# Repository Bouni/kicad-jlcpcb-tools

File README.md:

#  KiCAD JLCPCB tools

***

***

***

Plugin to generate all files necessary for JLCPCB board fabrication and assembly

- Gerber files
- Excellon files
- BOM file
- CPL file
- JLCPCB controlled-impedance workbook and self-contained HTML companion, when enabled for the board

Furthermore it lets you search the JLCPCB parts database and assign parts directly to the footprints which result in them being put into the BOM file.

On KiCad 10 boards with named [design variants](#design-variants-kicad-10),
compare and edit variants side by side and generate separate fabrication outputs.

## Installation 💾

### KiCAD PCM

Add my custom repo to *the Plugin and Content Manager*, the URL is:

```sh
https://raw.githubusercontent.com/Bouni/bouni-kicad-repository/main/repository.json
```

From there you can install the plugin via the GUI.

### Git

Clone this repo into your KiCad `scripting/plugins` folder.

> [!TIP]
> You can open the plugins directory directly from KiCad to avoid locating the path manually:
> In the *PCB Editor*, choose **Tools → External Plugins → Open Plugin Directory** (or **Reveal Plugin Folder in Finder** on macOS), or open **Preferences → PCB Editor → Action Plugins** and click the folder icon. From that directory, open a terminal and run `git clone https://github.com/Bouni/kicad-jlcpcb-tools.git`.

Alternatively, navigate to the folder in your terminal:

**Windows (Command Prompt)**

```cmd
cd "%USERPROFILE%\Documents\KiCad\<version>\scripting\plugins"
git clone https://github.com/Bouni/kicad-jlcpcb-tools.git
```

**Windows (PowerShell)**

```powershell
cd "$HOME\Documents\KiCad\<version>\scripting\plugins"
git clone https://github.com/Bouni/kicad-jlcpcb-tools.git
```

**Linux**

```sh
cd ~/.local/share/kicad/<version>/scripting/plugins
git clone https://github.com/Bouni/kicad-jlcpcb-tools.git
```

**macOS**

```sh
cd ~/Documents/KiCad/<version>/scripting/plugins
git clone https://github.com/Bouni/kicad-jlcpcb-tools.git
```

> [!NOTE]
> `<version>` can be `7.0`, `8.0`, `9.0`, or `X.YY` depending on the version you use. You may need to create the `scripting/plugins` folder if it does not exist.

After cloning, choose **Tools → External Plugins → Refresh Plugins** in the *PCB Editor* (or restart KiCad) to load the plugin.

### Flatpak :warning:

The Flatpak installation of KiCAD currently does not ship with pip and requests installed. The later is required for the plugin to work.
In order to get it working you can run the following 3 commands:

1. `flatpak run --command=sh org.kicad.KiCad`
2. `python -m ensurepip --upgrade`
3. `/var/data/python/bin/pip3 install requests`

See [issue #94](https://github.com/Bouni/kicad-jlcpcb-tools/issues/94) for more info.

## Usage 🥳

To access the plugin choose `Tools → External Plugins → JLCPCB Tools` from the *PCB Editor* menus

Checkout this screencast, it shows quickly how to use this plugin:

### Design variants (KiCad 10+)

Create named variants in KiCad and transfer them to the PCB to use the variant
table. Boards without named variants keep the ordinary parts table.

- **Compare variants side by side**, with Ref, Footprint, Side, PCB angle, and Correction columns fixed on the left when space permits. Ref stays fixed in narrower windows.
- **Spot differences quickly** through highlighted settings and yellow outlines around the affected variant’s cells in each component row.
- **Focus on differing component settings** with **Differences only** in the toolbar above the table.
- **Edit each variant independently:** Value, LCSC assignment, and BOM/POS/POP (populated) flags. Select components within one variant for batch assignments, flag changes, and copying.
- **Copy and paste selected components between variants:** Copy transfers Value, LCSC and BOM/POS/POP settings for every selected component; select the same components in another variant and Paste. Use **Copy cell value** for an individual value, or **Copy to variants…** to choose fields and destination variants.
- **Drag variant headers to reorder them** and bring variants together for comparison.
- **Compare price and stock availability** using compact indicators and hover details.
- **Choose an Output variant** to generate its BOM, placement, and fabrication files.
- **Review placement corrections for the Output variant** in the Correction column. Exact LCSC rules follow that variant's assigned part; pattern rules use Default's reference, Value, and placed footprint.

Assignments and flags are stored in the KiCad board; save the PCB to preserve edits.

The examples below use sample component data in the main JLCPCB Tools
window. Pointer and click cues make the actions easier to follow.

#### Edit settings and see differences

Change a setting in one variant to compare it with **Default**. Here,
turning off **POP** (populated) for **R4** in **Economy** highlights the
changed cell and outlines Economy’s cells in that row. The yellow outline
remains visible while the row is selected.

Turn POP back on to match Default and clear R4’s difference highlight.

#### Show differences only

Select **Differences only** in the toolbar above the table to focus on
differing component settings. In this example, enabling the checkbox
leaves **R1** and **R3** visible. Clear it to bring all five rows back.

#### Reorder variant columns

Drag a variant header to move its entire group of columns. Here,
**Premium** moves before **Economy**.

The translucent column preview follows the pointer, while the insertion
marker and **Drop before Economy** label show the destination. Release the
header to change the order to **Default**, **Premium**, **Economy**.

### Controlled impedance

Controlled impedance is an option that JLCPCB offers. To convey which traces should be impedance matched JLCPCB requires a `Required_impedance_control.xlsx` to be included in the design .zip file. If one is not included in your design package, JLCPCB will contact you and request that you provide this file.

It can be somewhat time consuming and repetative to update this file each time your layout changes, but not any more. This plugin can automatically generate the complete `Required_impedance_control.xlsx` file, including target impedances, reference layers AND all of the highlighted nets from the layout.

Generation also includes a self-contained `Required_impedance_control.html` companion in the board's Gerber ZIP for web viewing of the generated output.

Review tracking records the latest workbook-preview view time and each signal layer's approval time in that same database. Image-view dates are hidden during review; the HTML companion shows UTC and distinguishes current from historical captures/settings. Older records show **Not recorded**. Timestamps are saved with the configuration, not on Cancel, and do not replace the required image/layer review.

For inspection and regression testing, [two combined RF example boards](examples/impedance/README.md) cover short and long top/bottom/inner routes, single-ended and differential coplanar/noncoplanar designs, and layer transitions with different widths. These repository test assets are separate from production settings; their impedance dimensions are nominal, not solver-certified.

## Keyboard shortcuts

Windows can be closed with ctrl-w/ctrl-q/command-w/command-w (OS dependent) and escape.
Pressing enter in the keyword text box will start a search.

### Toggle BOM / CPL attributes

You can easily toggle the `exclude from BOM` and `exclude from CPL` attributes of one or multiple footprints.

### Select LCSC parts from the JLCPCB parts database

Select one or multiple footprints, click select part. You can select parts with equal value and footprint using the Select alike button.
In the upcoming modal dialog, search for parts, select the one of your choice and click select part.
The LCSC number of your selection will then be assigned to the footprints.

To type or paste an LCSC number instead, right-click the selected footprints and choose **Enter LCSC…**. It accepts a part number such as `C25804` or a product link copied from lcsc.com or jlcpcb.com. The number may be one the downloaded parts library does not list: JLC can still assemble LCSC-only parts it buys in through pre-order or global sourcing, and your library may be older than the part. The plugin asks once before assigning such a number. With no library downloaded there is nothing to check against, so it assigns without asking.

The part selector helps the same way: search for one LCSC number, and if the results don't show that exact part, a button beside the result count assigns it with one click.

### Automatic schematic saving

Closing JLCPCB Tools saves its LCSC assignments and supported BOM settings to
the project's schematics. The manual **Export to schematic** button has been
removed. On boards with design variants, this always saves **Default**;
selecting a named variant for fabrication does not change the schematic source.

A missing assignment field preserves the schematic's existing part number;
an explicit empty assignment clears it. Invalid or conflicting assignments are
preserved and reported while safe assignments still save. Footprints are linked
to symbols by KiCad's UUID paths, so changed or duplicate references do not
redirect a save. PCB-only footprints need no schematic update. Stale or ambiguous
links are preserved and reported.
For reused sheets, a shared field is updated only when every instance is linked
and agrees on that field. A linked multi-unit component updates all authenticated
units together; incomplete or ambiguous component membership is preserved.

Ordinary unassigned parts and PCB-only footprints close quietly. If an unassigned
PCB footprint has a part number in the schematic, use KiCad's **Update PCB from
Schematic** to transfer it to the board. This is an advisory, not a save failure.
When a conflict, invalid assignment, or unresolved link needs attention, the plugin keeps the complete report
at `jlcpcb/schematic-save-report.txt`, identifying affected footprints and the
reasons. Interactive closing also shows a warning; forced shutdown saves the
report without a prompt. A later complete save removes an outdated report.
Safe partial saves can complete; they do not authorize archival of active legacy
recovery data.

Projects that already have a `jlcpcb/project.db` see a one-time notice explaining
that the schematic is now the durable store. Before the first automatic write,
the plugin also keeps a permanent zip at
`jlcpcb/schematics-before-plugin-attributes.zip` so you can restore the previous
sheets if needed.

The plugin uses the project's associated schematics and preserves an `_old`
backup for each file it writes. Projects without an associated schematic close
without writing one. If a schematic is locked, the default **Cancel** keeps the
plugin open so you can close Schematic Editor and retry. **Save Anyway** approves
only the listed locks; **Close without saving** leaves the schematic unchanged.
Save errors also let you keep the window open or close without saving the
remaining changes. Earlier sheets may already have been saved if a later write
fails. A forced application shutdown cannot wait for these prompts: locked or
failed saves are logged and the window closes.

This saves schematic files. Use KiCad's PCB save command to persist changes to
the PCB itself. An already-open Schematic Editor does not reload exported files
automatically and can overwrite them if you choose **Save Anyway**.

### Where part assignments are stored

The live KiCad board is the sole source of LCSC assignments, with or without
named design variants. Selecting, pasting, or clearing a part updates the native
footprint fields or the selected variant's fields. **Save the PCB in KiCad to
persist these changes.** Refreshing the plugin reads the current board, including
edits made outside the plugin.

Both table modes recognize `LCSC`, `JLC`, and `JLCPCB` assignment fields,
optionally followed by `Part`, `Part Number`, `Part Num`, `Part No`, `PartNr`,
`PN`, `Number`, `Code`, or `ID`; case, spaces, and punctuation are ignored.
Conflicting or invalid assignments appear unassigned. Selecting or clearing a part updates
all recognized assignment fields together. Assignments and schematic saves preserve
existing alias names. A nonempty assignment creates a hidden `LCSC` field when no
recognized alias exists. Other prefixed fields, such as `JLCPCB Rotation` or
`LCSC custom code`, remain metadata; move part numbers from such fields into a
recognized assignment field.

*KiCad Symbol Properties with sample data for a 10k 0603 resistor (C25804).*

Previously, ordinary boards used database or CSV assignments while boards with
named variants read native fields. Editing or clearing Default, then removing
the last named variant, could therefore restore an obsolete database assignment.
Both modes now read and edit the board; the former schematic/database priority
setting no longer applies.

On opening, the plugin checks an existing `jlcpcb/project.db` for recoverable
legacy assignments before applying part preferences or displaying the initial
BOM. It imports a valid LCSC number only when the board assignment field is
missing and the reference, value, footprint, and BOM/POS flags exactly match
the historical row. Every linked schematic unit must also have no assignment or
the same part number. PCB-only footprints and projects confirmed to have no
schematic can recover directly into native fields, even if the PCB retains old
symbol paths. Unreadable project files and missing declared sheets do not count
as an absent schematic. KiCad 10's generated placeholder for a layout-only
project does not require a schematic file. Within a discovered hierarchy, stale
or ambiguous links remain unresolved.
Existing native values, explicit clears, invalid or conflicting
fields, unresolved links, and disagreeing shared instances are preserved.
Recovery imports neither stock nor flags and does not require a parts catalog.
Save the PCB to retain recovered assignments.

Once recovery is durable in the saved schematic or PCB, the active `part_info`
table is renamed to `part_info_retired`, preserving its rows and schema. Existing
archives remain intact; later archives use names such as `part_info_retired_2`.
The plugin rechecks the table's schema and data inside the archive transaction
so another window's changes cannot be archived using an outdated recovery check.
Before archival, the plugin reads the saved current PCB and sibling PCBs in the
same directory. macOS AppleDouble metadata sidecars are excluded. Recovery needed
by another board stays active, including recovery needed by temporary PCB copies.
The migration report names blocking sibling files and repeats only new notices;
acknowledgment does not allow archival. Obsolete rows can
be archived only when those saved boards confirm they are no longer needed;
an unsaved deletion or footprint change is insufficient. Native-only recovery
stays active until you explicitly save the PCB. The plugin never saves it for
you. Cancellation, incomplete saves, unresolved recovery, and unreadable saved
boards retain the recovery table for a later retry.

The durable `jlcpcb/legacy-migration-report.json` records the source board, old
legacy value, chosen native value or clear, and the reason for each recovery
decision, retaining original provenance and the latest board snapshot without
adding a full snapshot for every session. It survives schematic-report cleanup
and archival. When an existing native value or explicit clear supersedes a
legacy number, an interactive close
shows the previously unseen decisions once. Forced shutdown leaves that notice
pending for the next interactive close. Failed audit writes retain recovery data
and retry later without reapplying imported assignments. If the audit still cannot
be written, keep the plugin open to retry. Explicitly closing without the audit
or forcing shutdown can lose observations that could not be written to disk.

Archived assignments are never imported again, and legacy CSV files are never
automatically imported. Archival preserves generation counters, corrections,
other tables, and CSV files. Reading or refreshing assignments does not create
or modify `part_info`; the notice acknowledgment and generation counter use
the separate `metadata` table.

Supplier descriptions and other part details are cached in memory by LCSC
number and fetched again as needed. A part's assembly process and
Standard-only class are the exception: they are saved by LCSC number in
`global.db` in the data folder, so a board opened again shows them at once,
and they are fetched again in the background once they are 30 days old.
Stock and pricing come from the currently selected parts catalog; they are
not persisted as board assignments.

### Part preferences

Part preferences remember which LCSC part to use for a value and footprint combination across projects. Two independent settings are enabled by default:

- **Remember my part preferences** remembers each successful part selection or pasted LCSC assignment. The latest explicit assignment replaces the preference; opening a board does not change preferences.
- **Parts preferences fill in empty LCSC assignments** fills blank LCSC assignments once each time the plugin window opens. Existing assignments are preserved. DNP parts and parts excluded from BOM or POS are skipped.

Applying part preferences, including automatic filling on opening, writes the
native board fields. Save the PCB to keep those assignments.

Clearing an LCSC assignment keeps its part preference, so an eligible blank assignment may fill again on the next opening. Exclude the part or disable automatic filling to keep it blank. The right-click actions **Save part preferences** and **Apply part preferences** remain available even when automation is disabled. Use **Part preferences** to delete, import, or export preferences. Deleting a preference does not remove assignments from your boards.

### Generate fabrication data

Generate all necessary assembly files for your board with a simple click.

A new directory called `jlcpcb` is created, and in there, two separate folders are created, `gerber` and `production_files`.

In `gerber/<board-name>`, all necessary `*.gbr` and `*.drl` files are generated and zipped into the `production_files` folder, ready for upload to JLCPCB. Each board has a separate plotting directory.
The zipfile is named `GERBER-<projectname>.zip`

Also in the `production_files` folder, two files are generated, `BOM-<projectname>.csv` and `CPL-<projectname>.csv`.

Footprints are included into the BOM and CPL files according to their `exclude from BOM` and `exclude from POS` attributes.

A footprint's CPL `Mid X`/`Mid Y` is the center of the bounding box of its soldered pads: NPTH holes and paste-only pads are left out, and a footprint without soldered pads uses its own position.

Optional pre/post generation hook scripts can be configured in settings.

- The pre-hook runs before generation and can block generation on failure (with Continue/Cancel prompt).
- The post-hook runs only after successful generation.

See [HOOKS.md](HOOKS.md) for configuration details and available environment variables.

### Export Additional JLC Specific Layers

Some boards you have manufactured will require additional layers in your Gerber. For example, when manufacturing flex PCBs with a stiffener, JLC requires a layer outlining the stiffener layer (top/bottom), dimensions and the stiffener material properties (material, thickness etc). Export these additional JLC specific layers in your production files with a simple modification.

Additional layers can be exported by creating layers with `JLC_` as the prefix of the layer name. You can access and edit the layer names in *Board Setup/Board Stackup/Board Editor Layers*

This tool will automatically export all additional layers with the JLC_ prefix and add them to the production files in `GERBER-<projectname>.zip`

## Footprint rotation correction

JLCPCB seems to need corrected rotation information. @matthewlai implemented that in his [JLCKicadTools](https://github.com/matthewlai/JLCKicadTools) and I adopted his work in this plugin as well.
You can download Matthews file from GitHub and manage your own corrections in the Rotation manager.

See [Importing and repairing corrections](CORRECTIONS.md) for supported CSV
formats, validation rules, and recovery of invalid records from older versions.

## Icons

This plugin makes use of a lot of icons from the excellent [Material Design Icons](https://materialdesignicons.com/)

## Development

1. Fork repo
2. Git clone forked repo
3. Install pre-commit `pip install pre-commit`
4. Setup pre-commit `pre-commit run`
5. Create feature branch `git switch -c my-awesome-feature`
6. Make your changes
7. Commit your changes `git commit -m "Awesome new feature"`
8. Push to GitHub `git push`
9. Create PR

Make sure you make use of pre-commit hooks in order to format everything nicely with `black`
In the near future I'll add `ruff` / `pylint` and possibly other pre-commit-hooks that enforce nice and clean code style.

### Tests

With Docker and [`act`](https://nektosact.com/installation/) installed, run the
complete test workflow:

```sh
python scripts/run_tests.py
```

See [testing instructions](docs/testing.md) for architecture and output options.

### Settings

`default_settings.json` holds the settings a fresh install starts from and is the only
settings file tracked in git. The plugin writes the settings you actually use to
`settings.json` beside it, which is git-ignored, so toggling a checkbox while developing
no longer shows up as a change to commit.

On every launch the stored settings are layered over the defaults, so a setting added by
a newer version arrives with its default rather than being missing. Add new settings to
`default_settings.json`; `tests/test_settings_defaults.py` fails if a setting the code
reads has no default shipped for it.

## How to rebuild the parts database

The parts database is rebuilt by the [update_parts_database.yml GitHub workflow](https://github.com/Bouni/kicad-jlcpcb-tools/blob/main/.github/workflows/update_parts_database.yml)

You can reference the steps in the 'Update database' section for the commands to run locally.

## python libraries

lib/ contains the necessary python packages that may not be a part of the KiCad python distribution.

These packages include:

- packaging

To install a package, such as 'packaging':

```python
pip install packaging --target ./lib
```

To update these packages:

```python
pip install packaging --upgrade --target ./lib
```

Future versions of KiCad may have support for a requires.txt to automate this process.

## Standalone mode

Allows the plugin UI to be started without KiCAD, enabling debugging with an IDE like pycharm / vscode.

Standalone mode is under development.

### Limitations

- All board / footprint / value data are hardcoded stubs, see standalone_impl.py

### How to use

To use the plugin in standlone mode you'll need to identify three pieces of information specific to your Kicad version, plugin path, and OS.

#### Python

The <i><b>{KiCad python}</b></i> should be used, this can be found at different locations depending on your system:

| OS     | Kicad python                                                                                |
|--------|---------------------------------------------------------------------------------------------|
|Mac     | /Applications/KiCad/KiCad.app/Contents/Frameworks/Python.framework/Versions/3.9/bin/python3 |
|Linux   | /usr/bin/python3                                                                            |
|Windows | C:\Program Files\KiCad\8.0\bin\python.exe                                                   |

#### Working directory

The <i><b>{working directory}</b></i> should be your plugins directory, ie:

| OS     | Working dir                                                |
|--------|------------------------------------------------------------|
|Mac     | ~/Documents/KiCad/<version>/scripting/plugins/             |
|Linux   | ~/.local/share/kicad/<version>/scripting/plugins/          |
|Windows | %USERPROFILE%\Documents\KiCad\<version>\scripting\plugins\ |

> [!NOTE]  
> <version> can be 7.0, 8.0, 9.0, or X.YY depending on the version you use

#### Plugin folder name

The <i><b>{kicad-jlcpcb-tools folder name}</b></i> should be the name of the kicad-jlcpcb-tools folder.

- For Kicad managed plugins this may be like

> com_github_bouni_kicad-jlcpcb-tools

- If you are developing kicad-jlcpcb-tools this is the folder you cloned the kicad-jlcpcb-tools as.

#### Command line

- Change to the working directory as noted above
- Run the python interpreter with the <i><b>{kicad-jlcpcb-tools folder name}</b></i> folder as a module.

For example:

```sh
cd {working directory}
{kicad_python} -m {kicad-jlcpcb-tools folder name}
```

For example on Mac:

```sh
/Applications/KiCad/KiCad.app/Contents/Frameworks/Python.framework/Versions/3.9/bin/python3 -m kicad-jlcpcb-tools
```

For example on Linux:

```sh
cd ~/.local/share/kicad/8.0/scripting/plugins/ && python -m kicad-jlcpcb-tools
```

For example on Windows:

```cmd
& 'C:\Program Files\KiCad\8.0\bin\python.exe' -m kicad-jlcpcb-tools
```

#### IDE

- Configure the command line to be '{kicad_python} -m {kicad-jlcpcb-tools folder name}'
- Set the working directory to {working directory}

If using PyCharm or Jetbrains IDEs, set the interpreter to Kicad's python, <i><b>{Kicad python}</b></i> and under 'run configuration' select Python.

Click on 'script path' and change instead to 'module name',
entering the name of the kicad-jlcpcb-tools folder, <i><b>{kicad-jlcpcb-tools folder name}</b></i>.

## How to release new versions of this plugin

[bouni-kicad-repository](https://raw.githubusercontent.com/Bouni/bouni-kicad-repository/main/repository.json) contains the
files for the latest version of the plugin, in the format KiCAD expects from external plugins.

To release a new version of this plugin:

1. In the <b>kicad-jlcpcb-plugin</b> repository:
   1. Visit the releases page 
   1. Click on 'Choose a tag', enter the next release number, say 2025.04.01 for example, and click on 'Create Tag' 
   1. Click 'Generate release notes' 
   1. If the release notes looks good, click on 'Publish release' 
1. Automatically the new release will trigger the 'kicad-pcm' workflow which will:
   1. Pull the latest plugin tag
   1. Create the appropriate pcm archive
   1. Upload the zip as an asset to a new GitHub release
   1. benc-uk/workflow-dispatch@v1 is used to trigger the 'Rebuild repository' workflow in [bouni-kicad-repository](https://github.com/Bouni/bouni-kicad-repository)
1. Automatically in the <b>bouni-kicad-repository</b>, the 'Rebuild repository' (rebuild.yml) workflow runs 'generate.py'
   1. generate.py updates .json and the latest .zip file using the release assets from the kicad-jlcpcb-plugin repository
1. The plugin should now be visible to users via the plugin manager.

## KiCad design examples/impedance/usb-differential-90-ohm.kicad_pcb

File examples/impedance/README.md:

# Two impedance review boards

| Open in KiCad | Target | Connectors | Circuits |
| --- | ---: | --- | ---: |
| [Single-ended RF / 50 ohm](single-ended-50-ohm.kicad_pcb) | 50 Ω | SMA, two per circuit | 14 |
| [USB differential / 90 ohm / 8 mil pair gap](usb-differential-90-ohm.kicad_pcb) | 90 Ω | USB-C, two per circuit | 14 |

Each project is one continuous six-layer board with two labelled banks:
**noncoplanar** (surface microstrip / inner stripline) and **CPWG**
(surface / buried coplanar waveguide). Each bank contains top, inner and
bottom 2 mm and 120 mm controlled cores, plus a 150 mm three-layer route.
Lengths describe controlled cores; connector launches add electrical length.
Every circuit has unique nets; both members of each USB pair share one
highlight. Separate noncoplanar/CPWG net classes are visible in Board Setup.
Single-ended routes may use several capture regions to keep local traces
readable. Region counts in the manifest include all connector-launch copper;
native tracks remain intact and every track is represented exactly once.
USB controlled-run edge spacing is 8 mil (0.2032 mm).

Open the PCB, **Fill All Zones** (B), and select F.Cu, In2.Cu or B.Cu.
Use **Inactive Layer View Mode → Dim** to see nearby board context.
All six copper layers have GND pours. The adjacent reference layers are
In1.Cu for top, In1.Cu + In3.Cu for inner, and In4.Cu for bottom.
Keep each `.kicad_pro` and `.kicad_dru` beside its board: custom rules
hold noncoplanar same-layer GND zones 3 × the actual trace width away.
CPWG uses its close ground gap and stitching vias instead.

These are workflow/capture examples, **not solver-qualified impedance
coupons or USB-certified designs**. Consolidated geometry has not been
tested or run through DRC; review the workflow first. Canonical sources
omit generated fill caches. Plugin settings remain in the project database;
`manifest.json` is example metadata only.

[Design notes](../../docs/rf-impedance-fixtures.md) ·
[Embedded footprint sources and license](showcases/source-footprints/LICENSE.md)

Regenerate these two projects:

```sh
myenv/bin/python scripts/generate_rf_impedance_fixtures.py
```

Isolated matrix cases remain available on demand, outside this folder:

```sh
myenv/bin/python scripts/generate_rf_impedance_fixtures.py --legacy-matrix --output /tmp/isolated-rf-examples
```

The generator only writes its named artifacts. `--retire-legacy` moves
known old standalone board projects to a recoverable temporary backup;
unrelated files and the pinned footprint assets are left alone.

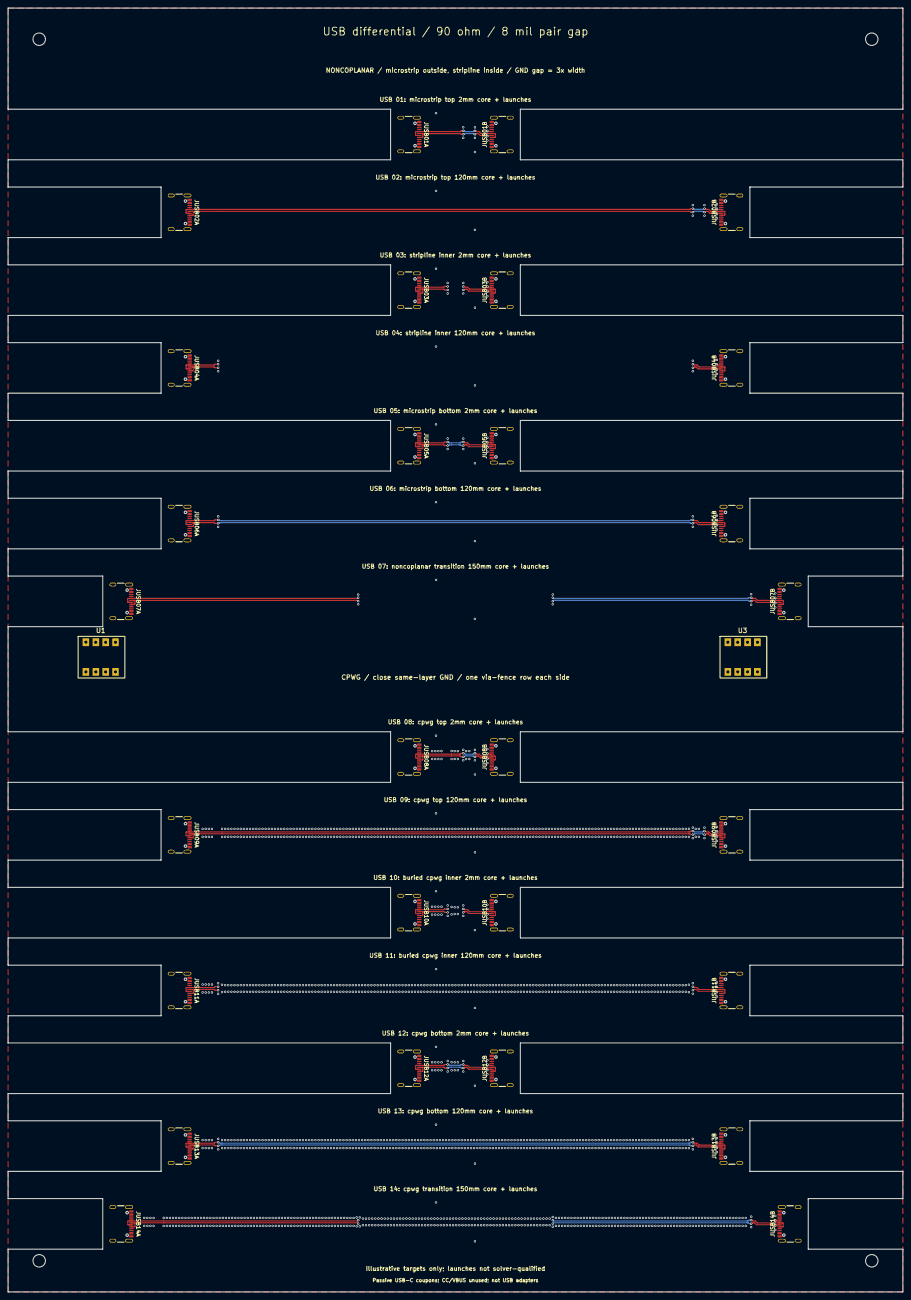
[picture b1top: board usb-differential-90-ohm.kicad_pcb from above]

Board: 6 copper layers, 230.0 x 330.0 mm, 30 parts (0 on the bottom side), 85 nets.

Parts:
JUSB01A, JUSB01B, JUSB02A, JUSB02B, JUSB03A, JUSB03B, JUSB04A, JUSB04B, JUSB05A, JUSB05B, JUSB06A, JUSB06B, JUSB07A, JUSB07B, JUSB08A, JUSB08B, JUSB09A, JUSB09B, JUSB10A, JUSB10B, JUSB11A, JUSB11B, JUSB12A, JUSB12B, JUSB13A, JUSB13B, JUSB14A, JUSB14B: USB-C; USB_C_Receptacle_GCT_USB4105-xx-A_16P_TopMnt_Horizontal
U1: U1
U3: U3

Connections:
GND: JUSB01A.A1, JUSB01A.A12, JUSB01A.B1, JUSB01A.B12, JUSB01A.SH, JUSB01B.A1, JUSB01B.A12, JUSB01B.B1, JUSB01B.B12, JUSB01B.SH, JUSB02A.A1, JUSB02A.A12, JUSB02A.B1, JUSB02A.B12, JUSB02A.SH, JUSB02B.A1, JUSB02B.A12, JUSB02B.B1, JUSB02B.B12, JUSB02B.SH, JUSB03A.A1, JUSB03A.A12, JUSB03A.B1, JUSB03A.B12, JUSB03A.SH, JUSB03B.A1, JUSB03B.A12, JUSB03B.B1, JUSB03B.B12, JUSB03B.SH, JUSB04A.A1, JUSB04A.A12, JUSB04A.B1, JUSB04A.B12, JUSB04A.SH, JUSB04B.A1, JUSB04B.A12, JUSB04B.B1, JUSB04B.B12, JUSB04B.SH, JUSB05A.A1, JUSB05A.A12, JUSB05A.B1, JUSB05A.B12, JUSB05A.SH, JUSB05B.A1, JUSB05B.A12, JUSB05B.B1, JUSB05B.B12, JUSB05B.SH, JUSB06A.A1, JUSB06A.A12, JUSB06A.B1, JUSB06A.B12, JUSB06A.SH, JUSB06B.A1, JUSB06B.A12, JUSB06B.B1, JUSB06B.B12, JUSB06B.SH, JUSB07A.A1, JUSB07A.A12, JUSB07A.B1, JUSB07A.B12, JUSB07A.SH, JUSB07B.A1, JUSB07B.A12, JUSB07B.B1, JUSB07B.B12, JUSB07B.SH, JUSB08A.A1, JUSB08A.A12, JUSB08A.B1, JUSB08A.B12, JUSB08A.SH, JUSB08B.A1, JUSB08B.A12, JUSB08B.B1, JUSB08B.B12, JUSB08B.SH, JUSB09A.A1, JUSB09A.A12, JUSB09A.B1, JUSB09A.B12, JUSB09A.SH, JUSB09B.A1, JUSB09B.A12, JUSB09B.B1, JUSB09B.B12, JUSB09B.SH, JUSB10A.A1, JUSB10A.A12, JUSB10A.B1, JUSB10A.B12, JUSB10A.SH, JUSB10B.A1, JUSB10B.A12, JUSB10B.B1, JUSB10B.B12, JUSB10B.SH, JUSB11A.A1, JUSB11A.A12, JUSB11A.B1, JUSB11A.B12, JUSB11A.SH, JUSB11B.A1, JUSB11B.A12, JUSB11B.B1, JUSB11B.B12, JUSB11B.SH, JUSB12A.A1, JUSB12A.A12, JUSB12A.B1, JUSB12A.B12, JUSB12A.SH, JUSB12B.A1, JUSB12B.A12, JUSB12B.B1, JUSB12B.B12, JUSB12B.SH, JUSB13A.A1, JUSB13A.A12, JUSB13A.B1, JUSB13A.B12, JUSB13A.SH, JUSB13B.A1, JUSB13B.A12, JUSB13B.B1, JUSB13B.B12, JUSB13B.SH, JUSB14A.A1, JUSB14A.A12, JUSB14A.B1, JUSB14A.B12, JUSB14A.SH, JUSB14B.A1, JUSB14B.A12, JUSB14B.B1, JUSB14B.B12, JUSB14B.SH, U1.1, U1.2, U1.3, U1.4, U1.5, U1.6, U1.7, U1.8, U3.1, U3.2, U3.3, U3.4, U3.5, U3.6, U3.7, U3.8
JUSB01A_UNUSED_VBUS_1: JUSB01A.A4, JUSB01A.B9
JUSB01A_UNUSED_VBUS_2: JUSB01A.A9, JUSB01A.B4
JUSB01B_UNUSED_VBUS_1: JUSB01B.A4, JUSB01B.B9
JUSB01B_UNUSED_VBUS_2: JUSB01B.A9, JUSB01B.B4
JUSB02A_UNUSED_VBUS_1: JUSB02A.A4, JUSB02A.B9
JUSB02A_UNUSED_VBUS_2: JUSB02A.A9, JUSB02A.B4
JUSB02B_UNUSED_VBUS_1: JUSB02B.A4, JUSB02B.B9
JUSB02B_UNUSED_VBUS_2: JUSB02B.A9, JUSB02B.B4
JUSB03A_UNUSED_VBUS_1: JUSB03A.A4, JUSB03A.B9
JUSB03A_UNUSED_VBUS_2: JUSB03A.A9, JUSB03A.B4
JUSB03B_UNUSED_VBUS_1: JUSB03B.A4, JUSB03B.B9
JUSB03B_UNUSED_VBUS_2: JUSB03B.A9, JUSB03B.B4
JUSB04A_UNUSED_VBUS_1: JUSB04A.A4, JUSB04A.B9
JUSB04A_UNUSED_VBUS_2: JUSB04A.A9, JUSB04A.B4
JUSB04B_UNUSED_VBUS_1: JUSB04B.A4, JUSB04B.B9
JUSB04B_UNUSED_VBUS_2: JUSB04B.A9, JUSB04B.B4
JUSB05A_UNUSED_VBUS_1: JUSB05A.A4, JUSB05A.B9
JUSB05A_UNUSED_VBUS_2: JUSB05A.A9, JUSB05A.B4
JUSB05B_UNUSED_VBUS_1: JUSB05B.A4, JUSB05B.B9
JUSB05B_UNUSED_VBUS_2: JUSB05B.A9, JUSB05B.B4
JUSB06A_UNUSED_VBUS_1: JUSB06A.A4, JUSB06A.B9
JUSB06A_UNUSED_VBUS_2: JUSB06A.A9, JUSB06A.B4
JUSB06B_UNUSED_VBUS_1: JUSB06B.A4, JUSB06B.B9
JUSB06B_UNUSED_VBUS_2: JUSB06B.A9, JUSB06B.B4
JUSB07A_UNUSED_VBUS_1: JUSB07A.A4, JUSB07A.B9
JUSB07A_UNUSED_VBUS_2: JUSB07A.A9, JUSB07A.B4
JUSB07B_UNUSED_VBUS_1: JUSB07B.A4, JUSB07B.B9
JUSB07B_UNUSED_VBUS_2: JUSB07B.A9, JUSB07B.B4
JUSB08A_UNUSED_VBUS_1: JUSB08A.A4, JUSB08A.B9
JUSB08A_UNUSED_VBUS_2: JUSB08A.A9, JUSB08A.B4
JUSB08B_UNUSED_VBUS_1: JUSB08B.A4, JUSB08B.B9
JUSB08B_UNUSED_VBUS_2: JUSB08B.A9, JUSB08B.B4
JUSB09A_UNUSED_VBUS_1: JUSB09A.A4, JUSB09A.B9
JUSB09A_UNUSED_VBUS_2: JUSB09A.A9, JUSB09A.B4
JUSB09B_UNUSED_VBUS_1: JUSB09B.A4, JUSB09B.B9
JUSB09B_UNUSED_VBUS_2: JUSB09B.A9, JUSB09B.B4
JUSB10A_UNUSED_VBUS_1: JUSB10A.A4, JUSB10A.B9
JUSB10A_UNUSED_VBUS_2: JUSB10A.A9, JUSB10A.B4
JUSB10B_UNUSED_VBUS_1: JUSB10B.A4, JUSB10B.B9
JUSB10B_UNUSED_VBUS_2: JUSB10B.A9, JUSB10B.B4
JUSB11A_UNUSED_VBUS_1: JUSB11A.A4, JUSB11A.B9
JUSB11A_UNUSED_VBUS_2: JUSB11A.A9, JUSB11A.B4
JUSB11B_UNUSED_VBUS_1: JUSB11B.A4, JUSB11B.B9
JUSB11B_UNUSED_VBUS_2: JUSB11B.A9, JUSB11B.B4
JUSB12A_UNUSED_VBUS_1: JUSB12A.A4, JUSB12A.B9
JUSB12A_UNUSED_VBUS_2: JUSB12A.A9, JUSB12A.B4
JUSB12B_UNUSED_VBUS_1: JUSB12B.A4, JUSB12B.B9
JUSB12B_UNUSED_VBUS_2: JUSB12B.A9, JUSB12B.B4
JUSB13A_UNUSED_VBUS_1: JUSB13A.A4, JUSB13A.B9
JUSB13A_UNUSED_VBUS_2: JUSB13A.A9, JUSB13A.B4
JUSB13B_UNUSED_VBUS_1: JUSB13B.A4, JUSB13B.B9
JUSB13B_UNUSED_VBUS_2: JUSB13B.A9, JUSB13B.B4
JUSB14A_UNUSED_VBUS_1: JUSB14A.A4, JUSB14A.B9
JUSB14A_UNUSED_VBUS_2: JUSB14A.A9, JUSB14A.B4
JUSB14B_UNUSED_VBUS_1: JUSB14B.A4, JUSB14B.B9
JUSB14B_UNUSED_VBUS_2: JUSB14B.A9, JUSB14B.B4
USB01_D+: JUSB01A.A6, JUSB01A.B6, JUSB01B.A6, JUSB01B.B6
USB01_D-: JUSB01A.A7, JUSB01A.B7, JUSB01B.A7, JUSB01B.B7
USB02_D+: JUSB02A.A6, JUSB02A.B6, JUSB02B.A6, JUSB02B.B6
USB02_D-: JUSB02A.A7, JUSB02A.B7, JUSB02B.A7, JUSB02B.B7
USB03_D+: JUSB03A.A6, JUSB03A.B6, JUSB03B.A6, JUSB03B.B6
USB03_D-: JUSB03A.A7, JUSB03A.B7, JUSB03B.A7, JUSB03B.B7
USB04_D+: JUSB04A.A6, JUSB04A.B6, JUSB04B.A6, JUSB04B.B6
USB04_D-: JUSB04A.A7, JUSB04A.B7, JUSB04B.A7, JUSB04B.B7
USB05_D+: JUSB05A.A6, JUSB05A.B6, JUSB05B.A6, JUSB05B.B6
USB05_D-: JUSB05A.A7, JUSB05A.B7, JUSB05B.A7, JUSB05B.B7
USB06_D+: JUSB06A.A6, JUSB06A.B6, JUSB06B.A6, JUSB06B.B6
USB06_D-: JUSB06A.A7, JUSB06A.B7, JUSB06B.A7, JUSB06B.B7
USB07_D+: JUSB07A.A6, JUSB07A.B6, JUSB07B.A6, JUSB07B.B6
USB07_D-: JUSB07A.A7, JUSB07A.B7, JUSB07B.A7, JUSB07B.B7
USB08_D+: JUSB08A.A6, JUSB08A.B6, JUSB08B.A6, JUSB08B.B6
USB08_D-: JUSB08A.A7, JUSB08A.B7, JUSB08B.A7, JUSB08B.B7
USB09_D+: JUSB09A.A6, JUSB09A.B6, JUSB09B.A6, JUSB09B.B6
USB09_D-: JUSB09A.A7, JUSB09A.B7, JUSB09B.A7, JUSB09B.B7
USB10_D+: JUSB10A.A6, JUSB10A.B6, JUSB10B.A6, JUSB10B.B6
USB10_D-: JUSB10A.A7, JUSB10A.B7, JUSB10B.A7, JUSB10B.B7
USB11_D+: JUSB11A.A6, JUSB11A.B6, JUSB11B.A6, JUSB11B.B6
USB11_D-: JUSB11A.A7, JUSB11A.B7, JUSB11B.A7, JUSB11B.B7
USB12_D+: JUSB12A.A6, JUSB12A.B6, JUSB12B.A6, JUSB12B.B6
USB12_D-: JUSB12A.A7, JUSB12A.B7, JUSB12B.A7, JUSB12B.B7
USB13_D+: JUSB13A.A6, JUSB13A.B6, JUSB13B.A6, JUSB13B.B6
USB13_D-: JUSB13A.A7, JUSB13A.B7, JUSB13B.A7, JUSB13B.B7
USB14_D+: JUSB14A.A6, JUSB14A.B6, JUSB14B.A6, JUSB14B.B6
USB14_D-: JUSB14A.A7, JUSB14A.B7, JUSB14B.A7, JUSB14B.B7

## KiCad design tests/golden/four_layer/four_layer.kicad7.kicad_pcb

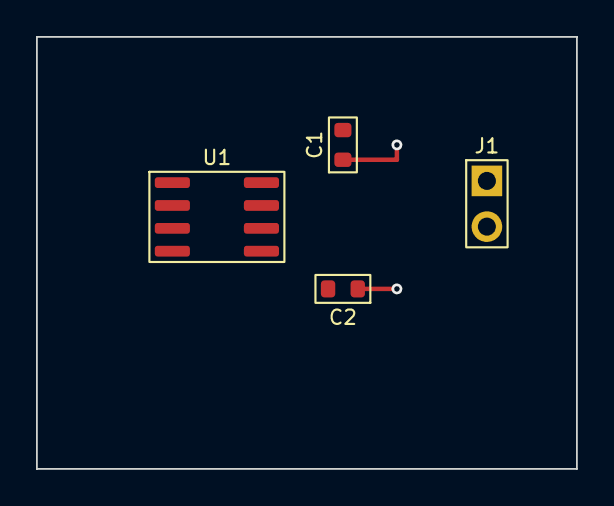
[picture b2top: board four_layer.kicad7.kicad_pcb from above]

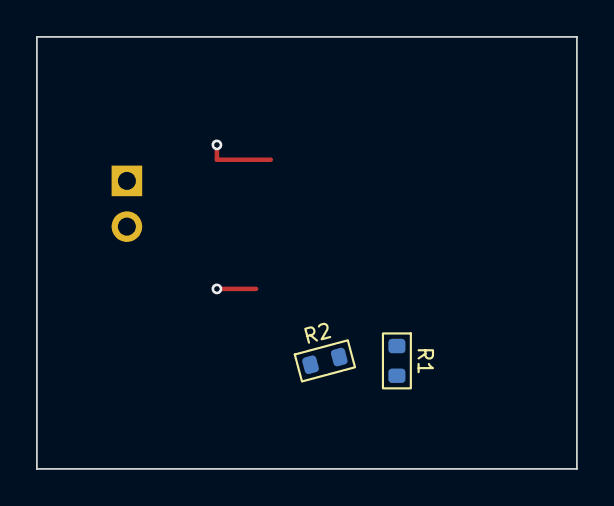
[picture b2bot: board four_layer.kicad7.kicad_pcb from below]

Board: 4 copper layers, 30.0 x 24.0 mm, 6 parts (2 on the bottom side), 2 nets.

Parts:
C1, C2: 100n; C_0603_1608Metric
J1: Conn_01x02; PinHeader_1x02_P2.54mm_Vertical
R1, R2: 22k; R_0603_1608Metric
U1: NE5532; SOIC-8_3.9x4.9mm_P1.27mm

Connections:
GND: C1.2, C2.2, J1.2
VCC: C1.1, C2.1, J1.1

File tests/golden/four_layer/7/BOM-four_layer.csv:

Comment,Designator,Footprint,LCSC,Quantity
100n,"C1,C2",C_0603_1608Metric,C14663,2
22k,"R1,R2",R_0603_1608Metric,C31850,2
Conn_01x02,J1,PinHeader_1x02_P2.54mm_Vertical,C49257,1
NE5532,U1,SOIC-8_3.9x4.9mm_P1.27mm,C7426,1

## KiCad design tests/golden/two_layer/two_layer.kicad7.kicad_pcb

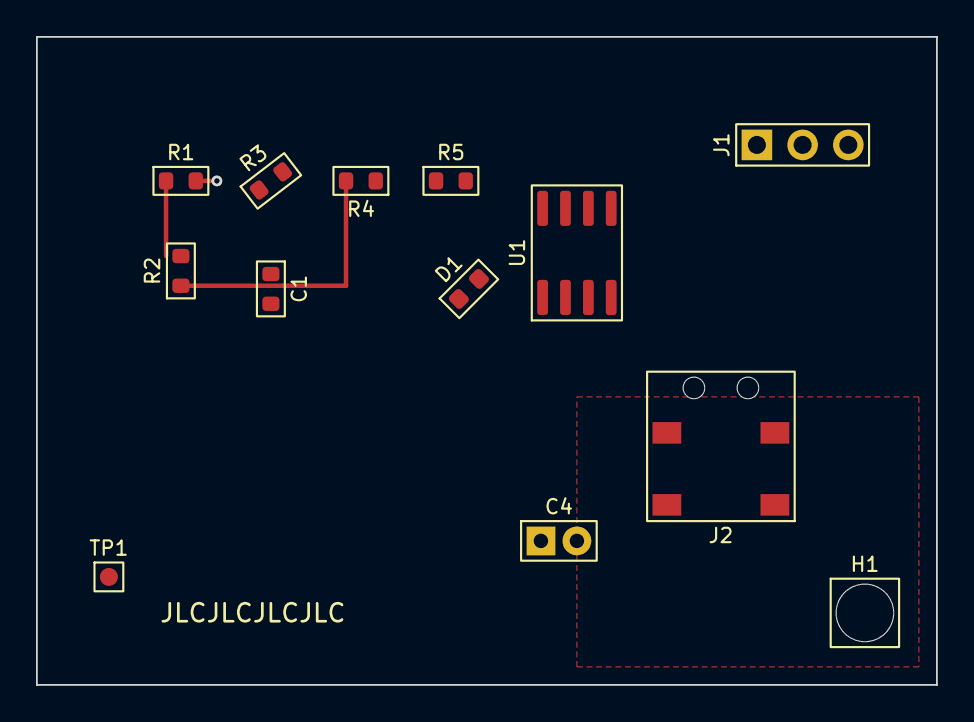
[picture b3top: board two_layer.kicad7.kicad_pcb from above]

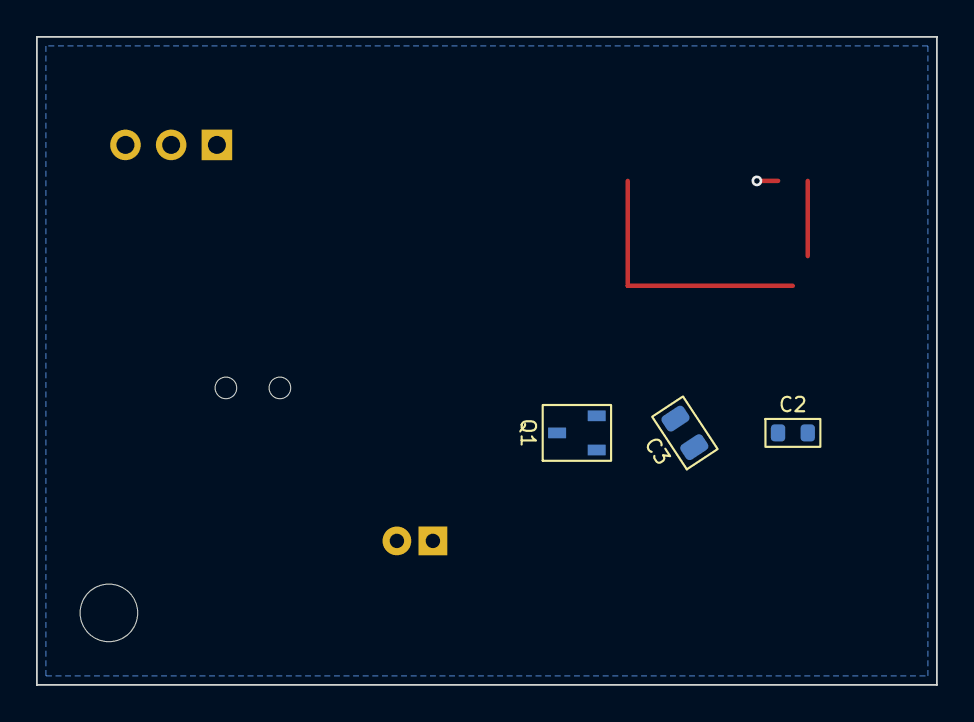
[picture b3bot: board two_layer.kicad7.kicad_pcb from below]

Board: 2 copper layers, 50.0 x 36.0 mm, 16 parts (3 on the bottom side), 3 nets.

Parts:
C1, C2: 100n; C_0603_1608Metric
C3: 10u; C_0805_2012Metric
C4: 47u; CP_Radial_D5.0mm_P2.00mm
D1: LED; LED_0603_1608Metric
H1: MountingHole; MountingHole_3.2mm_M3
J1: Conn_01x03; PinHeader_1x03_P2.54mm_Vertical
J2: Jack; Jack_3.5mm_SMD_Pegs
Q1: MMBT3904; SOT-23
R1, R2, R3: 10k; R_0603_1608Metric
R4: 4k7; R_0603_1608Metric
R5: 1k; R_0603_1608Metric
TP1: TP; TestPoint_Pad_D1.0mm
U1: LM358; SOIC-8_3.9x4.9mm_P1.27mm

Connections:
A: C4.1, J1.2, R1.1, R2.1
B: J1.3, R2.2, R4.1
GND: C4.2, J1.1, R1.2

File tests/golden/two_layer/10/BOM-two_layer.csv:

Comment,Designator,Footprint,LCSC,Quantity
100n,"C1,C2",C_0603_1608Metric,C14663,2
10k,"R1,R2,R3",R_0603_1608Metric,C25804,3
10u,C3,C_0805_2012Metric,C15850,1
47u,C4,CP_Radial_D5.0mm_P2.00mm,C43350,1
4k7,R4,R_0603_1608Metric,C23162,1
Conn_01x03,J1,PinHeader_1x03_P2.54mm_Vertical,C2337,1
Jack,J2,Jack_3.5mm_SMD_Pegs,C431535,1
LM358,U1,SOIC-8_3.9x4.9mm_P1.27mm,C7950,1
MMBT3904,Q1,SOT-23,C20526,1
LED,D1,LED_0603_1608Metric,,1

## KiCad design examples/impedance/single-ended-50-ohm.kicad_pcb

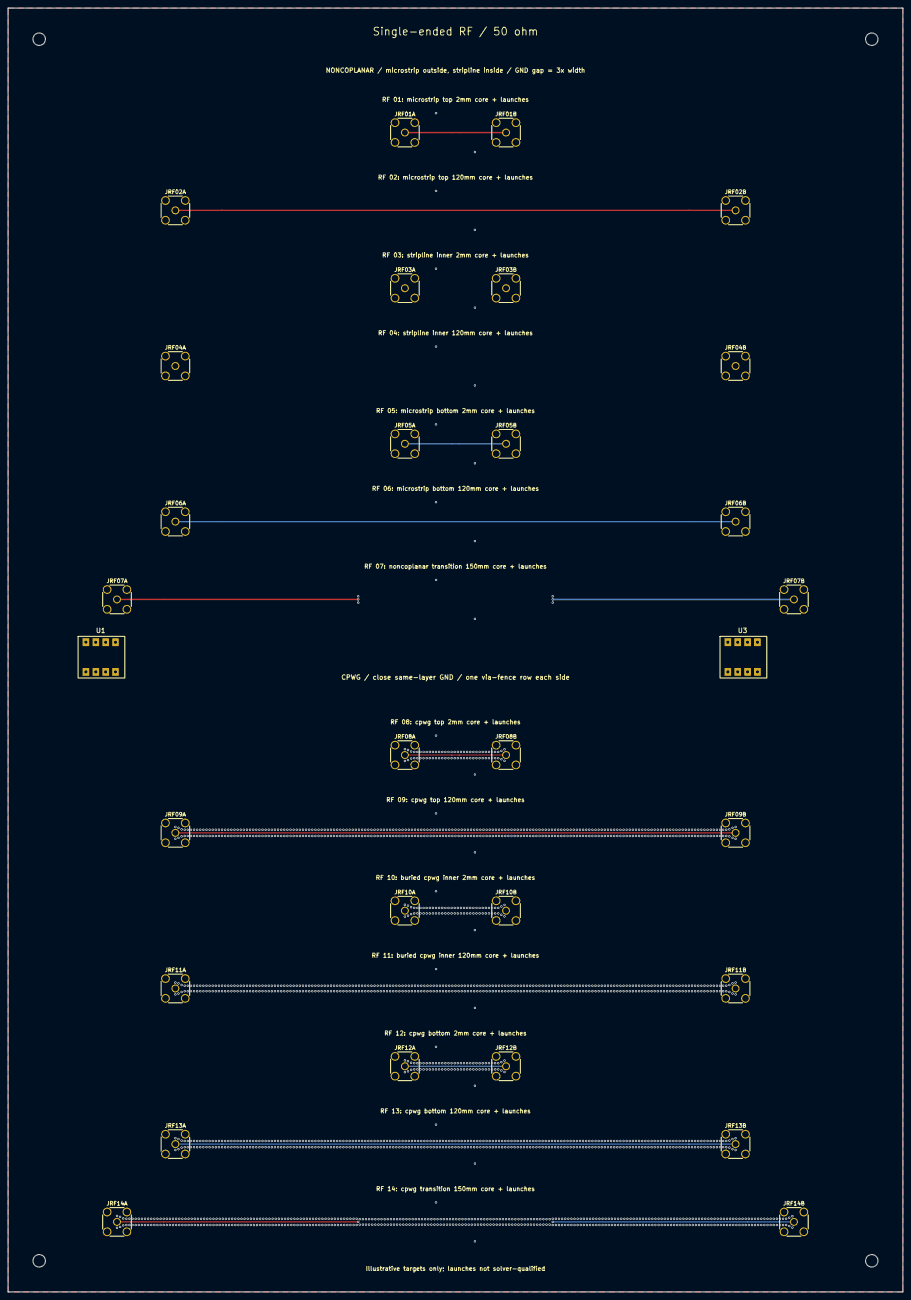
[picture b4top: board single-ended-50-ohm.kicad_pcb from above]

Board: 6 copper layers, 230.0 x 330.0 mm, 30 parts (0 on the bottom side), 15 nets.

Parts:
JRF01A, JRF01B, JRF02A, JRF02B, JRF03A, JRF03B, JRF04A, JRF04B, JRF05A, JRF05B, JRF06A, JRF06B, JRF07A, JRF07B, JRF08A, JRF08B, JRF09A, JRF09B, JRF10A, JRF10B, JRF11A, JRF11B, JRF12A, JRF12B, JRF13A, JRF13B, JRF14A, JRF14B: SMA_Amphenol_132134_Vertical
U1: U1
U3: U3

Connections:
GND: JRF01A.2, JRF01B.2, JRF02A.2, JRF02B.2, JRF03A.2, JRF03B.2, JRF04A.2, JRF04B.2, JRF05A.2, JRF05B.2, JRF06A.2, JRF06B.2, JRF07A.2, JRF07B.2, JRF08A.2, JRF08B.2, JRF09A.2, JRF09B.2, JRF10A.2, JRF10B.2, JRF11A.2, JRF11B.2, JRF12A.2, JRF12B.2, JRF13A.2, JRF13B.2, JRF14A.2, JRF14B.2, U1.1, U1.2, U1.3, U1.4, U1.5, U1.6, U1.7, U1.8, U3.1, U3.2, U3.3, U3.4, U3.5, U3.6, U3.7, U3.8
RF01: JRF01A.1, JRF01B.1
RF02: JRF02A.1, JRF02B.1
RF03: JRF03A.1, JRF03B.1
RF04: JRF04A.1, JRF04B.1
RF05: JRF05A.1, JRF05B.1
RF06: JRF06A.1, JRF06B.1
RF07: JRF07A.1, JRF07B.1
RF08: JRF08A.1, JRF08B.1
RF09: JRF09A.1, JRF09B.1
RF10: JRF10A.1, JRF10B.1
RF11: JRF11A.1, JRF11B.1
RF12: JRF12A.1, JRF12B.1
RF13: JRF13A.1, JRF13B.1
RF14: JRF14A.1, JRF14B.1
